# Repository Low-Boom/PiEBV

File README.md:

# PiEBV

A pulse-timing box for particle image velocimetry (PIV), built around a Raspberry Pi Pico 2 W. It
triggers two laser drivers and synchronizes up to six event cameras. It is controlled over USB,
and also over Wi-Fi after the network link is set up.

> **Hardware status:** Firmware timing has not yet been verified on a physical board. Complete the
> [first-board checks](docs/FIRST_BOARD_CHECKS.md#first-board-checks) before connecting a laser driver or camera.
> The network (Wi-Fi) link has not run on a board either: do the
> [network checks](docs/FIRST_BOARD_CHECKS.md#network-checks) before you rely on it.

## Quick start

With the assembled board, a Pico 2 W, a USB-C PD charger that supplies 15 V, and a micro-USB data
cable:

```
python -m pip install platformio
pio run
```

1. Follow the [first-board checks](docs/FIRST_BOARD_CHECKS.md#first-board-checks) before applying power or
   connecting equipment.
2. Flash `.pio/build/pico2w/firmware.uf2`: hold **BOOTSEL** while connecting the Pico's micro-USB
   cable, then copy the UF2 to the `RP2350` drive. Flash with the Pico out of the board or J17
   unplugged.
3. Seat the Pico components-up, USB toward the board's left edge. Set J10 to **2-3** and J18, J19
   and J21 to **1-2** for the 50 Ω scope checks; leave J11 empty until instructed to check the outputs.
4. Connect the 15 V charger to J17 and the Pico's micro-USB to the computer. Open the Pico's serial
   port, enable local echo, and send `*IDN?`. The reply starts with `PiEBV,`.
5. Follow [Hardware setup](docs/SETUP.md#hardware-setup) to check the laser outputs with a scope before
   connecting laser drivers or cameras.

**Contents:** [Quick start](#quick-start) · [Documentation](#documentation) ·
[What it does](#what-it-does) · [Safety](#safety) · [The board](#the-board) ·
[Connecting](#connecting) · [Most-used commands](#most-used-commands) ·
[Repository layout](#repository-layout)

---

## Documentation

The README gives the overview. The pages below give the detail.

| Page | What it holds | Who needs it |
|---|---|---|
| [docs/SAFETY.md](docs/SAFETY.md) | The safety rules in detail: starting and stopping, laser outputs, cameras and jumpers | Everyone, before the lasers are armed for the first time |
| [docs/SETUP.md](docs/SETUP.md) | Hardware setup step by step, first-board checks, jumpers, J12, seating the Pico, power | Anyone who sets up a board |
| [docs/CONNECTING.md](docs/CONNECTING.md) | USB serial, web GUI, Python scripting, network (Wi-Fi) | Operators and script writers |
| [docs/COMMANDS.md](docs/COMMANDS.md) | Command reference (SCPI): rules, commands, timing, status registers, errors, Wi-Fi set-up | Operators and script writers |
| [docs/TROUBLESHOOTING.md](docs/TROUBLESHOOTING.md) | Symptoms, likely causes and fixes | Anyone with a problem |
| [docs/FIRMWARE_BUILD.md](docs/FIRMWARE_BUILD.md) | Building from source, timing checks, protocol check, network check, signal simulation | Firmware developers |
| [Hardware.md](Hardware.md) | Hardware reference: pins, power, signal chains, connectors | Hardware developers |
| [docs/DESIGN_NOTES.md](docs/DESIGN_NOTES.md) | Design notes: index of the design pages in `docs/design/` (layout, power, signals, firmware, network link), Rev 2 changes | Hardware and firmware developers |
| [docs/design/NETWORK.md](docs/design/NETWORK.md) | Design of the network link: decisions, rules for `DISARM`, radio fault handling, verification | Firmware developers |
| [docs/FIRST_BOARD_CHECKS.md](docs/FIRST_BOARD_CHECKS.md) | The full first-board checks, with exact test points | Anyone who tests a newly assembled board |
| [docs/MANUFACTURING.md](docs/MANUFACTURING.md) | Fabrication and assembly notes | Anyone who orders or assembles a board |
| [docs/EVK4_HARNESS.md](docs/EVK4_HARNESS.md) | The EVK4 camera harness | Users of Prophesee EVK4 cameras |
| [fab/jlc/JLC_ORDER.md](fab/jlc/JLC_ORDER.md) | The JLCPCB order checklist | Anyone who orders a board |
| [tools/rev2/README.md](tools/rev2/README.md) | The scripts that build the Rev 2 board | Hardware developers |
| [tools/signal_sim/README.md](tools/signal_sim/README.md) | The transmission-line simulation of the timing nets | Hardware developers |

---

## What it does

| Output | Connector | What it is for |
|---|---|---|
| **Laser 1** (CH1) | BNC J7 | Trigger for the first laser driver: a 5 V pulse (with J18 set to match the input), of the set pulse width (`:PULS:WIDT`), at the set frequency (`:FREQ`) |
| **Laser 2** (CH2) | BNC J8 | Trigger for the second laser driver: the same pulse, starting exactly the set delay (`:PULS:DOUB:DEL`) after Laser 1 |
| **Sync** | Camera ports J1–J6 | A steady 1 MHz clock that all six cameras keep time by |
| **Trigger** (the marker) | Camera ports J1–J6 | A pulse at the same instant as every Laser 1 pulse. Each camera records it as a timestamp in its data. (Jumper J10 can switch the cameras to the Laser 1 pulse itself instead.) |
| **Pixel reset** | Camera ports J1–J6 | Holds the camera sensors blank between flash pairs. Controlled only by PiEBV (`:PIX:GATE`) |
| **External Sync Out** | BNC J12 | A copy of the camera trigger (the marker, or Laser 1 with J10 on 1-2) for other equipment: a 5 V pulse, with J21 set to match the input |

- Every signal to the cameras is **1.8 V** (IDS cameras, J22 open) or **3.3 V** (Prophesee EVK4
  cameras, J22 fitted). The laser outputs and External Sync Out are **5 V**.
- The camera signal level comes from a power mux (U20). Its default input is 1.8 V: with J22 open,
  two pull-up resistors in parallel (R34 and R70) select 1.8 V. A shunt on J22 pulls the select pin low and selects
  3.3 V.
- Each camera line has a **47 Ω series resistor on the board** (R52–R69), between the buffer and
  the camera port. It terminates the camera cable at the source. The camera cables need no
  resistors.
- The camera lines of each group have **equal length** on the board, from the buffer to the series
  resistor: Sync 74.082 mm, Trigger 43.584 mm, pixel reset 51.472 mm (spread below 0.001 mm in
  each group, KiCad's length reading).
- Times are set in steps of **6.667 ns** (one tick of the Pico's 150 MHz clock), or **3.333 ns**
  with a shunt on the clock jumper J20 (a 300 MHz overclock; see [Jumpers](#jumpers)).
  Every query returns the exact value the hardware will produce, so you never have to correct for
  the step size.
- Both laser pulses share one pulse width and one frequency.
- The firmware sets **no laser-driver limits** (pulse width, duty, spacing). Set what your driver is
  rated for. It only stops the pulses from running into each other.

PiEBV was designed for two **PicoLas LDP-V** laser-diode drivers (models 10-70 and 240-100) and six
**IDS uEye UE-39B0XCP-E** event cameras. Board revision 2 can also drive six **Prophesee EVK4**
cameras at 3.3 V (see the [EVK4 harness](docs/EVK4_HARNESS.md)). Other drivers with a 5 V trigger input should work too, with
the output mode (J18/J19) set to match their input.

---

## Safety

### The short version

1. **The lasers start off.** At every power-up and every reset the laser outputs are DISARMED. They
   pulse only after you send `:OUTP ON`.
2. **Typing `DISARM` stops them at once.** `:OUTP OFF` also stops them.
3. **Three things must all be true** for the lasers to pulse. Remove any one and they stop:
   - the firmware is ARMED;
   - a shunt is on **J11 pins 1-2** (or a closed E-stop switch is wired there);
   - a 15 V USB-C charger is plugged into **J17**.
4. **Unplugging the computer does not stop the lasers.** Use J11 or J17 for that. A lost network
   link does not stop them either. With Wi-Fi set up, `:OUTP ON` can also come from the network.
5. **Set each output's mode (J18, J19, J21) before you connect anything to it.**
6. **One laser driver per output.** Never split an output with a BNC tee, and never join J7 and J8.
7. **Cameras:** build the harness with wires 2, 3, 4, 5 and 7 only, and set every camera to sync
   slave.

The rules in detail are in [docs/SAFETY.md](docs/SAFETY.md).

---

## The board

The board is a **EuroCard, 160 × 100 mm**. Orientation used below: the board is landscape (160 mm
wide), seen from the top side. All connectors are on the two short edges: the Pico's micro-USB,
TP3 and, at the bottom, the USB-C connector J17 on the **left** edge, and only the three BNCs on
the **right** edge. The Pico plugs into two horizontal sockets at the top left, with its micro-USB at
the left edge, and the six camera ports run in one row along the bottom. The two USB ports are
labelled on the board: **`CONTROL / PROGRAM — PICO MICRO-USB`** (commands and firmware) and
**`POWER ONLY — USB-C PD 15 V`** (J17). The long (160 mm) edges have no parts within 2.5 mm, so the
board fits EuroCard card guides and slotted enclosures.

```
             +------------------------------------------------------------+
 Pico USB    |= Pico 2 W, in J15 (top row)                        J18 J7 =|  Laser 1 (BNC)
 = CONTROL   |  and J14 (bottom row)        J10 (trigger select)          |
             |= TP3 (1 MHz scope)  J20 (clock)                    J19 J8 =|  Laser 2 (BNC)
             |  J12 offset field            J11 (laser enable)            |
             |                                                   J21 J12 =|  External Sync Out (BNC)
 USB-C       |= J17                                                       |
 = POWER ONLY|       J1   J2   J3   J4   J5   J6   (camera ports)         |
             +------------------------------------------------------------+
```

(Not to scale. J18, J19 and J21 are the output-mode jumpers. J22, at the top centre, sets the camera signal level.
J23, the fan header, is at the bottom left, between mounting hole MH3 and camera port J1.
The status LEDs are near the top edge. Images of the board are in
[Hardware.md](Hardware.md#board-views).)

### Connectors

| Ref | What | Connect to | Notes |
|---|---|---|---|
| **J1–J6** | Camera ports 1–6 (2×5 IDC headers) | Each camera's 8-pin I/O cable (header pin *n* = camera pin *n*) | Pin 2, 7 ground · 3 pixel reset · 4 trigger · 5 sync · 1, 6, 8, 9, 10 not connected. All signals **1.8 V** (J22 open, IDS cameras) or **3.3 V** (J22 fitted, Prophesee EVK4 with the [EVK4 harness](docs/EVK4_HARNESS.md)). Each signal has a 47 Ω series resistor on the board. Pin 1 is the top-left pin. |
| **J7** | BNC, Laser 1 (CH1) | First laser driver's trigger input | Mode set by J18 |
| **J8** | BNC, Laser 2 (CH2) | Second laser driver's trigger input | Mode set by J19 |
| **J12** | BNC, External Sync Out | Equipment that must follow the camera trigger (50 Ω or Hi-Z input) | Mode set by J21. See [J12](docs/SETUP.md#j12--external-sync-out) |
| **J17** | USB-C, **power only** | A USB-C PD charger that offers 15 V | No data. Commands and firmware go through the Pico's own micro-USB. |
| **J10** | Camera trigger source (jumper) | A shunt | See [Jumpers](#jumpers) |
| **J11** | Laser enable (jumper) | A shunt, or a normally-closed E-stop switch | See [Jumpers](#jumpers) |
| **J18**, **J19**, **J21** | Output mode (jumpers; J18 = Laser 1, J19 = Laser 2, J21 = External Sync Out) | A shunt | See [Jumpers](#jumpers) |
| **J20** | Clock jumper, 2-pin header right of the Pico, below the J14 row | Nothing (150 MHz), or a shunt (300 MHz overclock) | See [Jumpers](#jumpers). Leave it open unless that Pico passed the soak test. |
| **TP3** | 2-pin header on the left edge, below the Pico | A scope | Pin 1 = the 1 MHz sync straight from the Pico (3.3 V) · pin 2 = ground |
| **J22** | Camera signal level, 2-pin header at the top centre | Nothing (1.8 V, IDS cameras), or a shunt (3.3 V, Prophesee EVK4) | See [Jumpers](#jumpers). **Never fit it with an IDS camera connected.** |
| **J23** | Fan supply, 2-pin header at the bottom left, marked `J23  FAN 12V` and `0.2 A MAX` | One 2-wire 12 V DC cooling fan of 40 mm, 200 mA maximum | Pin 1 (`+`, the top pin) = 12 V · pin 2 (`-`) = ground. The fan runs when the charger on J17 gives 15 V. There is no firmware control. The header has no key: connect the fan with the correct polarity. Do not fit a shunt on J23: it shorts the fan supply to ground. Do not connect a fan to the 12 V supply of the laser drivers. |
| **TP4–TP9** | Bare test pads at the top centre, marked `12V`, `5V`, `3V3`, `1V8`, `VCAM`, `GND` | A multimeter | Supply rails |

### Jumpers

Pin 1 always has the square pad. Change J22 with the power off.

| Jumper | Function | Positions | Default |
|---|---|---|---|
| **J10** | Camera trigger source | 1-2: every Laser 1 pulse (only while ARMED) · 2-3: the marker · none: no camera triggers | **2-3** |
| **J11** | Laser enable | 1-2: lasers enabled (the firmware must also be ARMED) · 2-3 or none: lasers off | **1-2** to run. Leave it empty until you check the outputs. |
| **J18** | Laser 1 output mode | 1-2: 50 Ω mode · 2-3: Hi-Z mode · none: wrong, always fit a shunt | **1-2** (for the LDP-V) |
| **J19** | Laser 2 output mode | as J18 | as J18 |
| **J21** | External Sync Out mode | 1-2: 50 Ω mode · 2-3: Hi-Z mode · none: wrong, always fit a shunt | **1-2** |
| **J20** | Clock jumper (2 pins) | open: 150 MHz, the rated clock · shunt: 300 MHz overclock | **open** |
| **J22** | Camera signal level (2 pins) | open: 1.8 V (IDS cameras) · shunt: 3.3 V (Prophesee EVK4) | **open** |

The board labels, the E-stop wiring and the full description of each jumper are in
[docs/SETUP.md](docs/SETUP.md#jumpers).

### Status LEDs

The LEDs near the top edge show the state of the board.

| LED | Colour | Meaning when lit |
|---|---|---|
| `12V OK` | green | The USB-C charger gave 15 V and the 12 V supply of the output drivers is good. Dark: the laser outputs and J12 cannot pulse. |
| `ARMED` | red | The lasers can fire: the firmware is ARMED, J11 is on 1-2 (or the E-stop switch is closed) and `12V OK` is lit. |
| `3V3` | blue | The camera ports are at 3.3 V (J22 fitted). Dark: 1.8 V. |
| `L1`, `L2` | red | A pulse left the Laser 1 / Laser 2 output driver. One flash for each pulse; on continuously above about 70 pulses a second. |
| `SYNC` | yellow | A pulse left the External Sync Out driver (J12). |

The LEDs are indicators only. Do not use a dark `ARMED` LED as proof that the lasers are off: an
LED can fail. To make the lasers safe, send `DISARM`, open J11 or unplug J17.

### Pico and power

Seat the Pico components up, with its micro-USB connector at the left edge. Connect a USB-C PD
charger that offers 15 V to J17. Connect the Pico's micro-USB to the computer. A 12 V cooling fan
on J23 runs when the charger gives 15 V. On a 5 V-only charger it normally does not turn. The details are in
[Seating the Pico](docs/SETUP.md#seating-the-pico) and [Power](docs/SETUP.md#power).

---

## Connecting

1. Use the Pico's micro-USB port. J17 carries power only.
2. Open the Pico's serial port. The port needs no driver.
   ```
   pio device monitor --echo                 # PlatformIO; add -p COM7 if needed
   ```
3. Turn on local echo. The firmware does not echo what you type.
4. Do not use 1200 baud. 115200 is usual.
5. Type `*IDN?` and press Enter. The reply starts with `PiEBV,`.
6. Type `:SYST:ECHO ON` to get a reply to each setting and each error in the terminal. Without
   it, a setting gives no reply.

Other terminals, the web GUI and Python scripting are in [docs/CONNECTING.md](docs/CONNECTING.md).

### Network (Wi-Fi)

A Pico 2 W can also take the commands over Wi-Fi, on TCP port 4242 of an existing network (open,
or WPA2 with a shared passphrase). Set it up one time over USB, with the lasers DISARMED:

```
:SYST:COMM:WLAN:SSID "Lab Network"
:SYST:COMM:WLAN:PASS "correct horse"
:SYST:COMM:WLAN ON
:SYST:ERR?                       ->  0,"No error"
:SYST:COMM:WLAN:LINK?;IPAD?      ->  CONNECTED,"";"192.168.1.37"
```

Then connect to the address that `:SYST:COMM:WLAN:IPAD?` gives, for example
`python tools/piebv_gui/piebv_gui.py --connect socket://192.168.1.37:4242`. The web GUI has a card
for the same set-up.

- The network link has **no password and no encryption**: each computer that can reach the board
  can arm the lasers. Use it only on a network that you control.
- A lost network link does not disarm.
- The link has not been tested on a board.

The details and the limits are in [docs/CONNECTING.md](docs/CONNECTING.md#network-wi-fi).

## Most-used commands

| Command | Unit | Default | What it sets or returns |
|---|---|---|---|
| `:FREQ <f>`, `:FREQ?` | Hz | 1000 | How many pulse pairs per second |
| `:PULS:WIDT <t>`, `:PULS:WIDT?` | s | 100 ns | Length of both laser pulses |
| `:PULS:DOUB:DEL <t>`, `:PULS:DOUB:DEL?` | s | 10 µs | Time from the start of the Laser 1 pulse to the start of the Laser 2 pulse. `0` makes them start together. |
| `:OUTP ON` | – | disarmed | Allow the laser pulses (arm) |
| `DISARM` | – | – | Stop the laser pulses at once; recognised anywhere in what you type. `:OUTP OFF` also disarms. |
| `:OUTP?` | – | – | The arm state: `0` or `1` |
| `:SYST:ERR?` | – | – | The next entry of the error queue, or `0,"No error"` |
| `:SYST:ECHO ON` | – | off | A reply to each setting and error, for a terminal |
| `*IDN?` | – | – | Board and firmware version (the git commit it was built from) |
| `*RST` | – | – | Disarm and set the default settings |
| `:SYST:COMM:WLAN …` | – | off | The Wi-Fi state and set-up ([details](docs/COMMANDS.md#wi-fi-set-up)) |
| `:SYST:HELP:HEAD?` | – | – | The list of all commands |

- Times are in seconds and frequencies in hertz. Add a suffix: `:PULS:WIDT 100 NS`,
  `:PULS:DOUB:DEL 10 US`, `:FREQ 2 KHZ`. A number without a suffix is in seconds or hertz.
- A query ends in `?` and returns the realized value, for example `1.000000000E-07` for 100 ns.
- A setting gives no reply. An error goes into the error queue: read it with `:SYST:ERR?`.
- One line can hold more than one command, separated by `;`:
  `:FREQ 15;:PULS:WIDT 100 NS;DOUB:DEL 10 US`.

All commands, limits and errors are in [docs/COMMANDS.md](docs/COMMANDS.md). If something
does not work, see [docs/TROUBLESHOOTING.md](docs/TROUBLESHOOTING.md).

---

## Repository layout

| Path | Contents |
|---|---|
| `src/` | Firmware: `main.cpp` (start-up, arming, crash watchdog), `protocol.*` (SCPI commands, on USB and on the network link), `net_link.*` (Wi-Fi link of a Pico 2 W), `tcp_link.*` (its TCP server), `wifi_config.h` (Wi-Fi set-up values and flash record), `pulse_timing.h` (timing maths and checks), `pio_pulse.*` (PIO programs), `sync_clock.*` (1 MHz SYNC clock), `clock_mode.*` (clock jumper: 150 or 300 MHz at boot), `laser_gate.*` (laser output gate), `board.h` (pin map) |
| `platformio.ini` | Build configuration (`pico2w` and `pico2` builds) |
| `tools/piebv_example.py` | Python example script |
| `tools/piebv_gui/` | Web GUI: settings, timing chart and console in the browser |
| `tools/piebv_sim/` | Simulator: the firmware's command code built for a computer, for trying the GUI and scripts without a board, and `scpi_check.py`, which checks the SCPI replies |
| `tools/timing_check/` | Timing checks run on a computer |
| `tools/net_check/` | Checks of the network link's connection handling, run on a computer: against a model of lwIP, and against lwIP's own sources |
| `tools/signal_sim/` | Transmission-line simulation of the timing nets (KiCad's ngspice) |
| `PiEBV_Pico.kicad_pro` / `.kicad_sch` / `.kicad_pcb` | **Current hardware:** KiCad project of the 4-layer board |
| `Hardware.md` | [Full hardware reference](Hardware.md) |
| `fab/` | Manufacturing: master parts list `fab/PiEBV_Pico_BOM.csv` (with the design-constraint notes), gerbers and drill files, and `fab/jlc/` JLCPCB assembly files and [order checklist](fab/jlc/JLC_ORDER.md) |
| `libs/`, `fp-lib-table`, `sym-lib-table` | Project-local KiCad symbols and footprints |
| `tools/jlc_cpl/` | Corrects the JLC placement file to JLC's own footprints (see its README) |
| `tools/eurocard/` | Builds the Rev 1 EuroCard board from the 126 × 126 mm hand layout: placement, KiCadRoutingTools routing, checks (see its README) |
| `tools/rev2/` | Builds the current Rev 2 board from the Rev 1 EuroCard board: camera level select, series resistors in the camera lines, new camera routing with equal lengths, status LEDs, power islands, cooling fan supply, checks, fab export (see its README) |
| `docs/` | The documentation pages (see [Documentation](#documentation)), the [EVK4 camera harness](docs/EVK4_HARNESS.md) and the board images (`docs/img/`) |
| `docs/reports/` | Earlier design review reports |

## License

PiEBV is distributed under **OCL v1.1 + RnD v1**: the
[Open Community License v1.1](https://github.com/OpenCommunityLicence/OpenCommunityLicence)
with the add-on condition
[Research & Development v1](https://github.com/OpenCommunityLicence/OpenCommunityLicence/blob/main/addons/RnD-v1.md).
The full text is in [LICENSE](LICENSE). The board silkscreen shows `OCL v1.1 + RnD v1`.

Summary (for orientation only; the text in [LICENSE](LICENSE) applies):

- **Non-commercial use:** you may use, copy, modify and hack PiEBV. If you distribute a
  derivative, you must distribute it under OCL and keep the RnD v1 condition.
- **Commercial use:** only for internal research and development: experiments and prototyping
  to develop your own creations that are not derived from PiEBV. You must not use PiEBV or its
  derivatives for manufacturing outside this scope without a separate business licence. You
  must not copy or replicate them for a commercial purpose without a separate business licence
  or repair licence, except for your internal right to repair.
- **Text and data mining:** systematic or automated text or data mining of PiEBV is not
  permitted without explicit permission.
- Components that are under a licence that is not compatible with OCL keep their own licence.

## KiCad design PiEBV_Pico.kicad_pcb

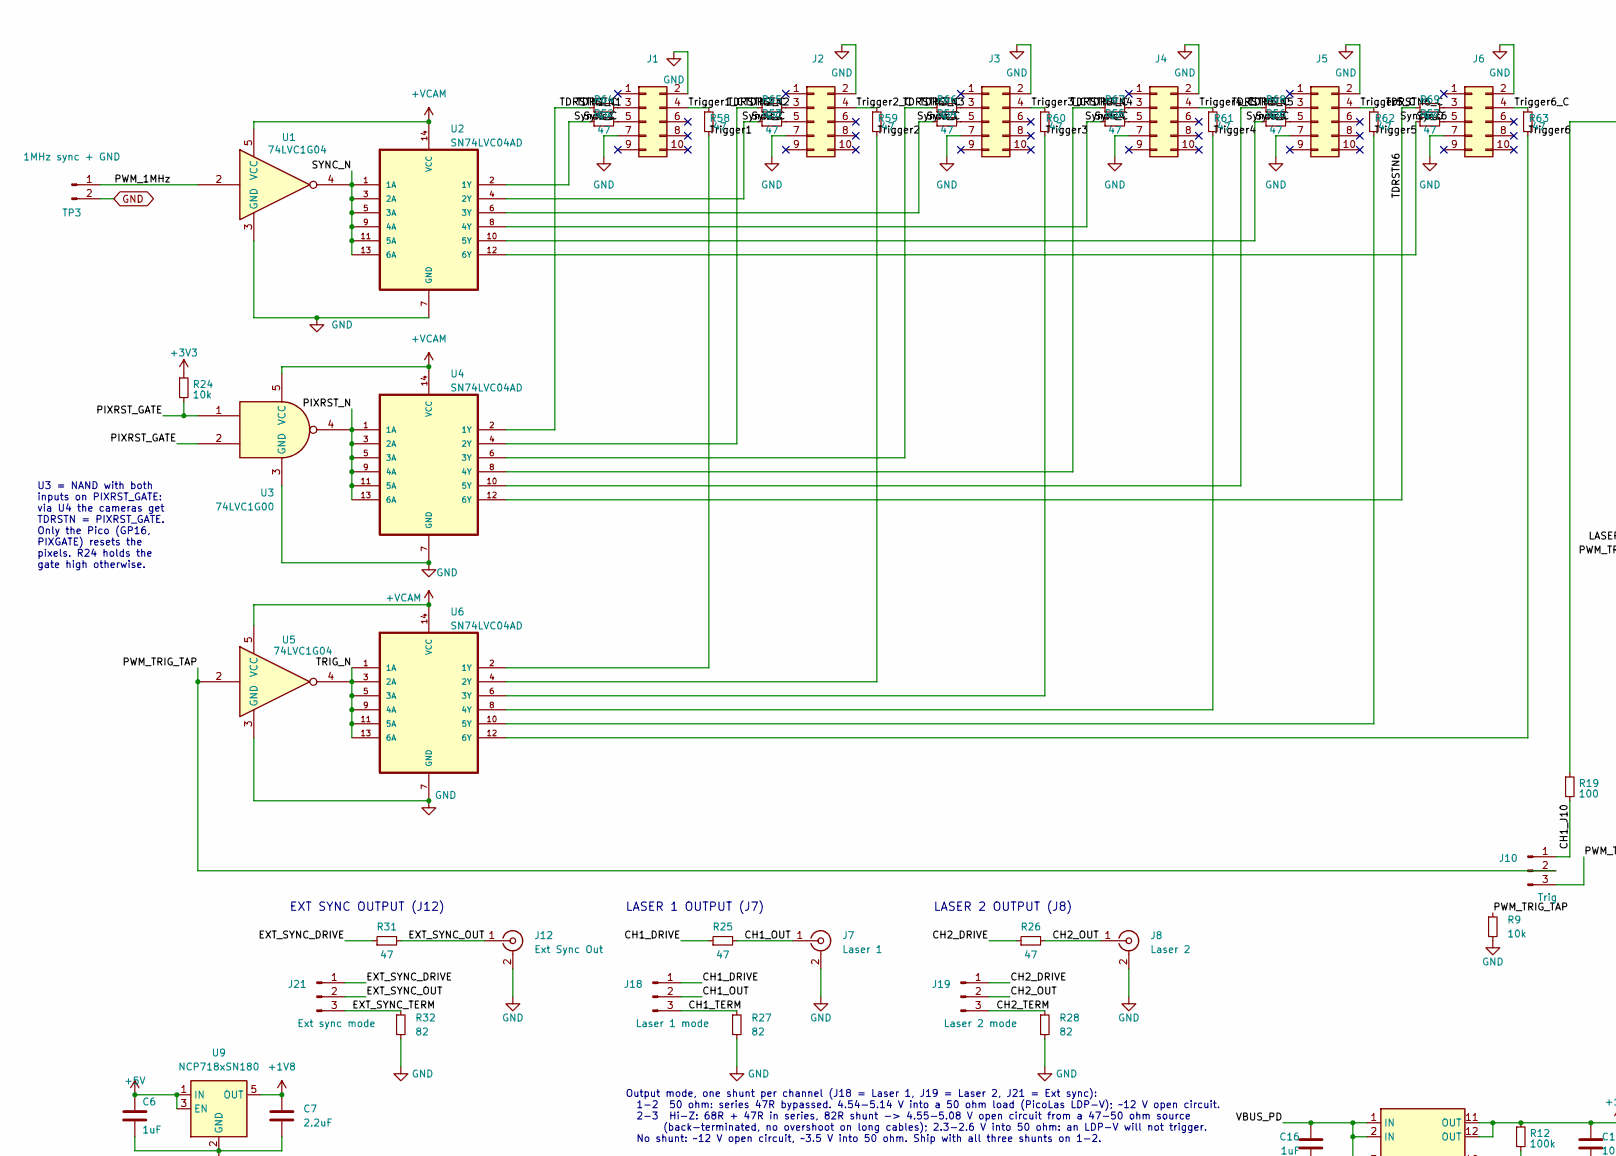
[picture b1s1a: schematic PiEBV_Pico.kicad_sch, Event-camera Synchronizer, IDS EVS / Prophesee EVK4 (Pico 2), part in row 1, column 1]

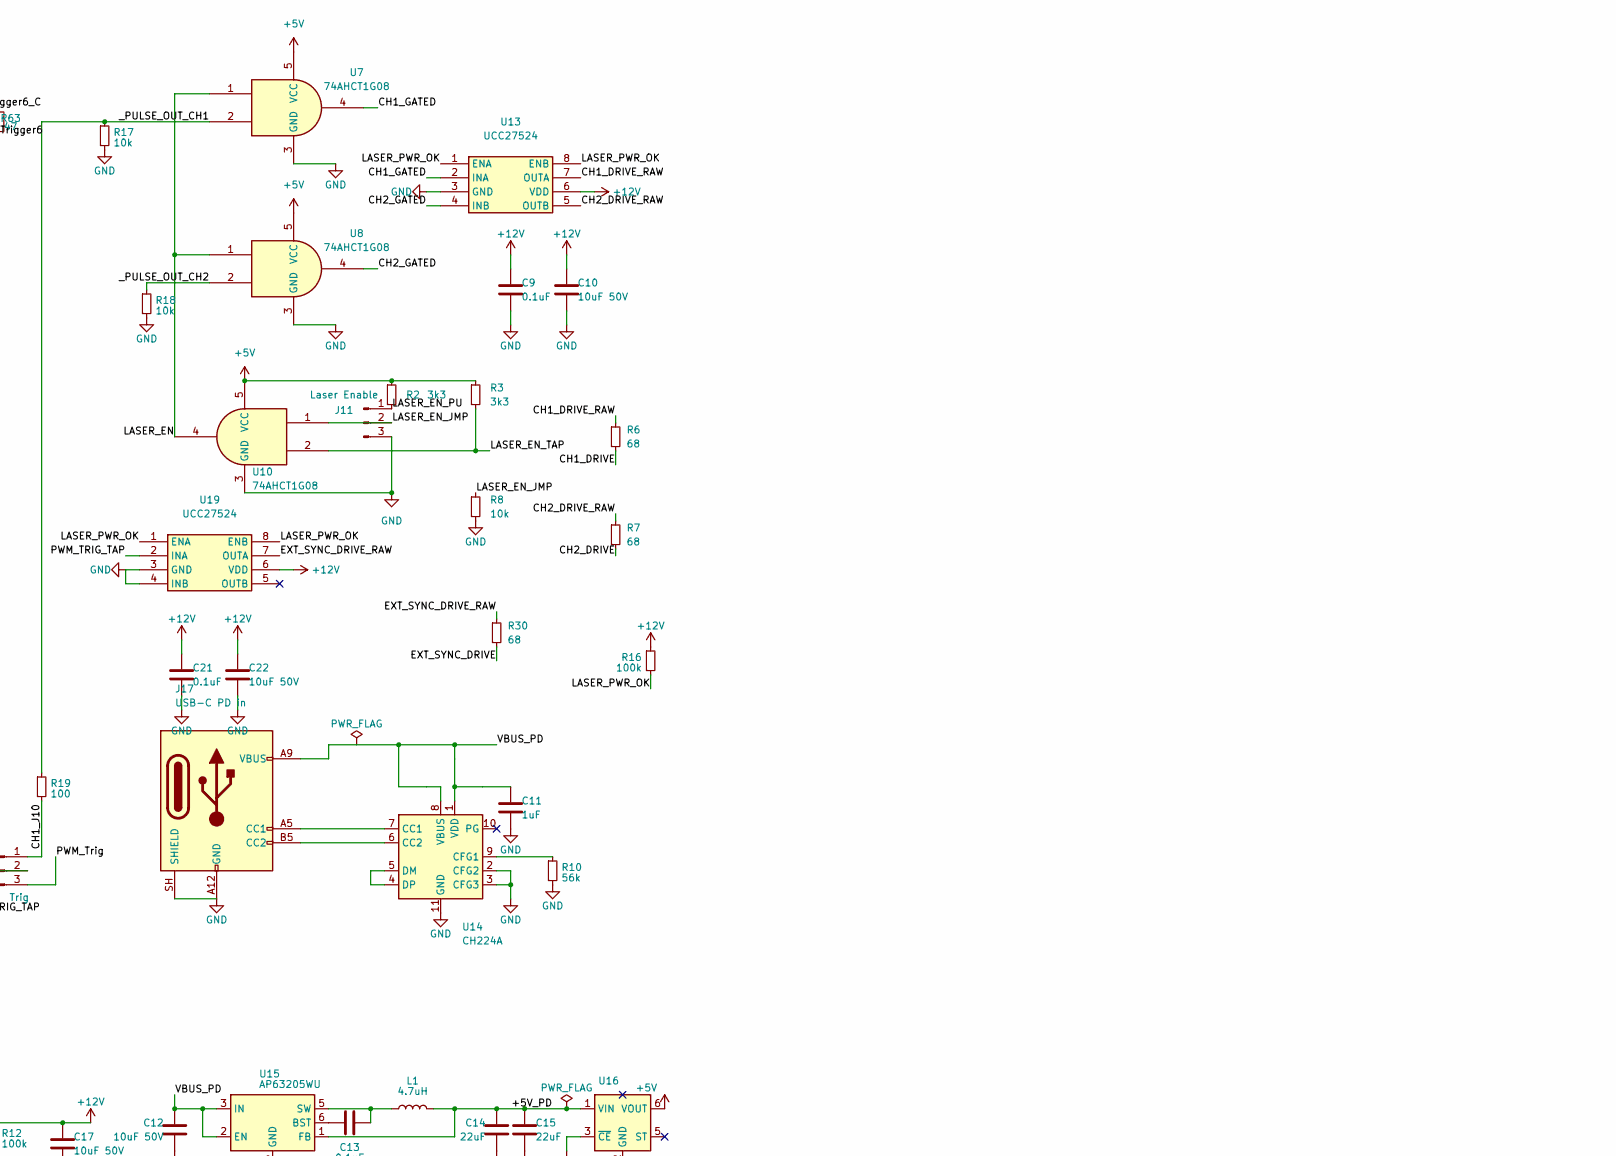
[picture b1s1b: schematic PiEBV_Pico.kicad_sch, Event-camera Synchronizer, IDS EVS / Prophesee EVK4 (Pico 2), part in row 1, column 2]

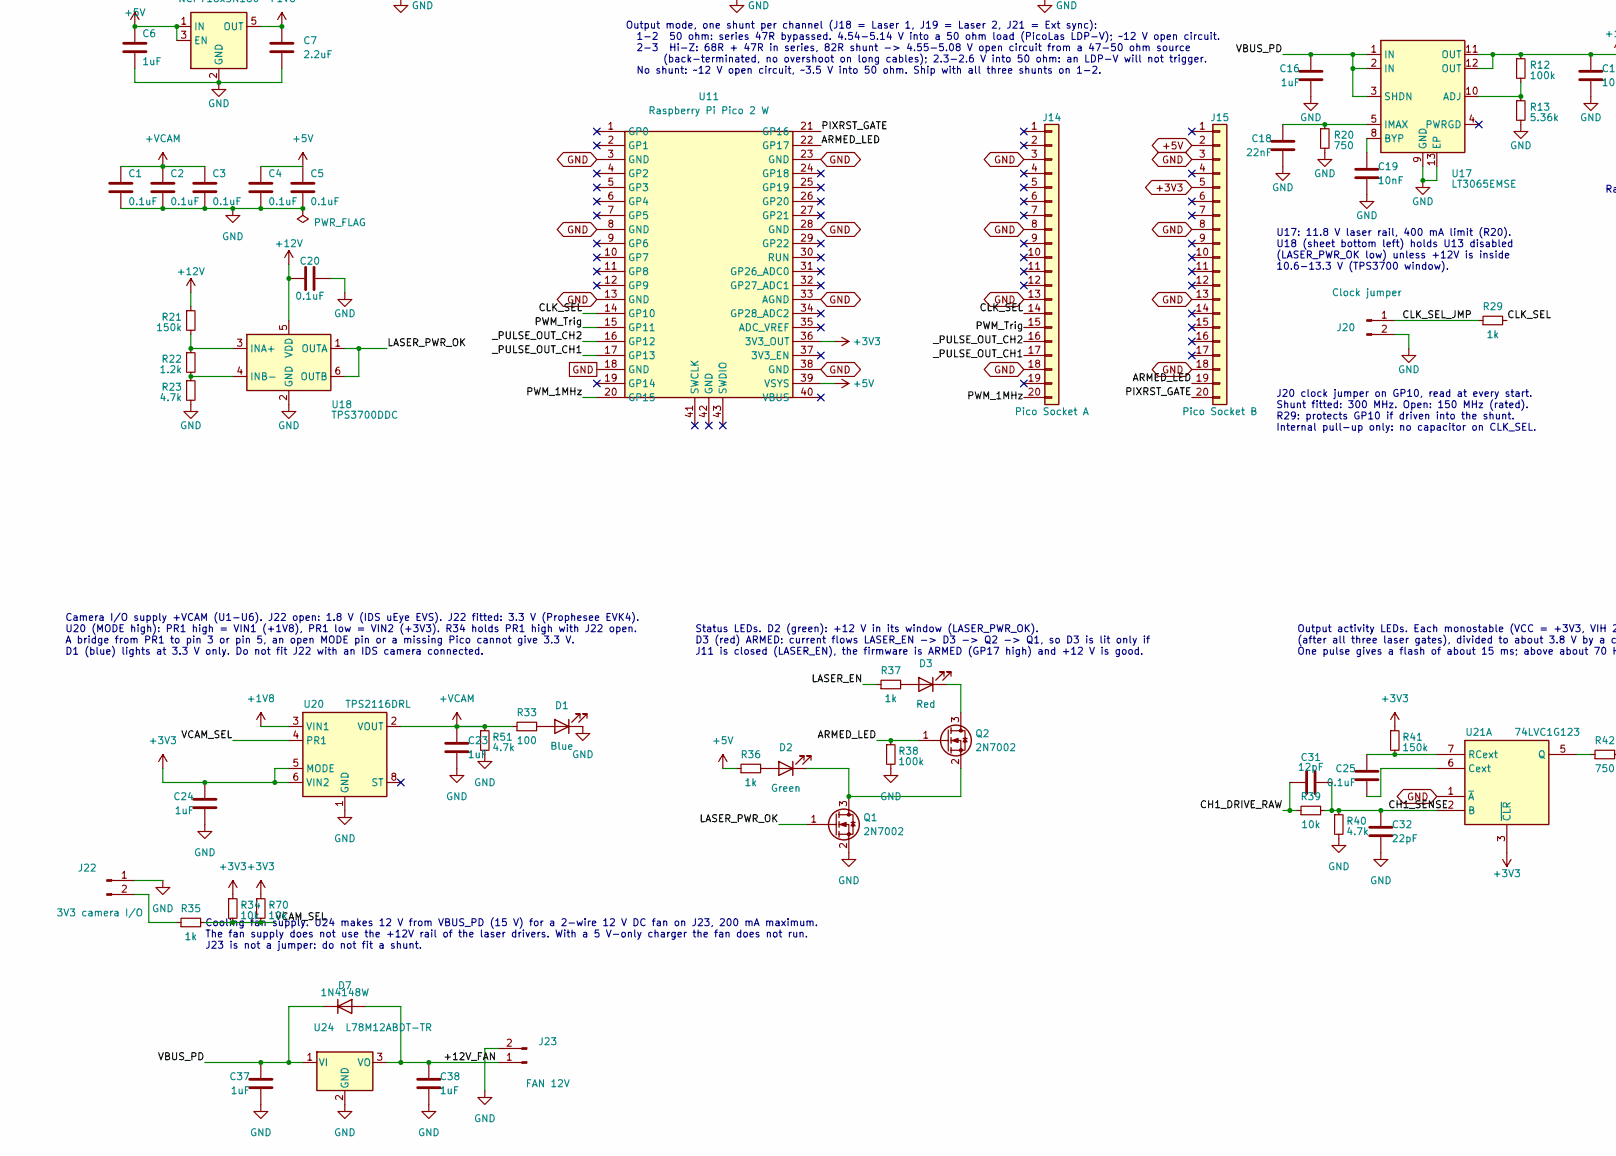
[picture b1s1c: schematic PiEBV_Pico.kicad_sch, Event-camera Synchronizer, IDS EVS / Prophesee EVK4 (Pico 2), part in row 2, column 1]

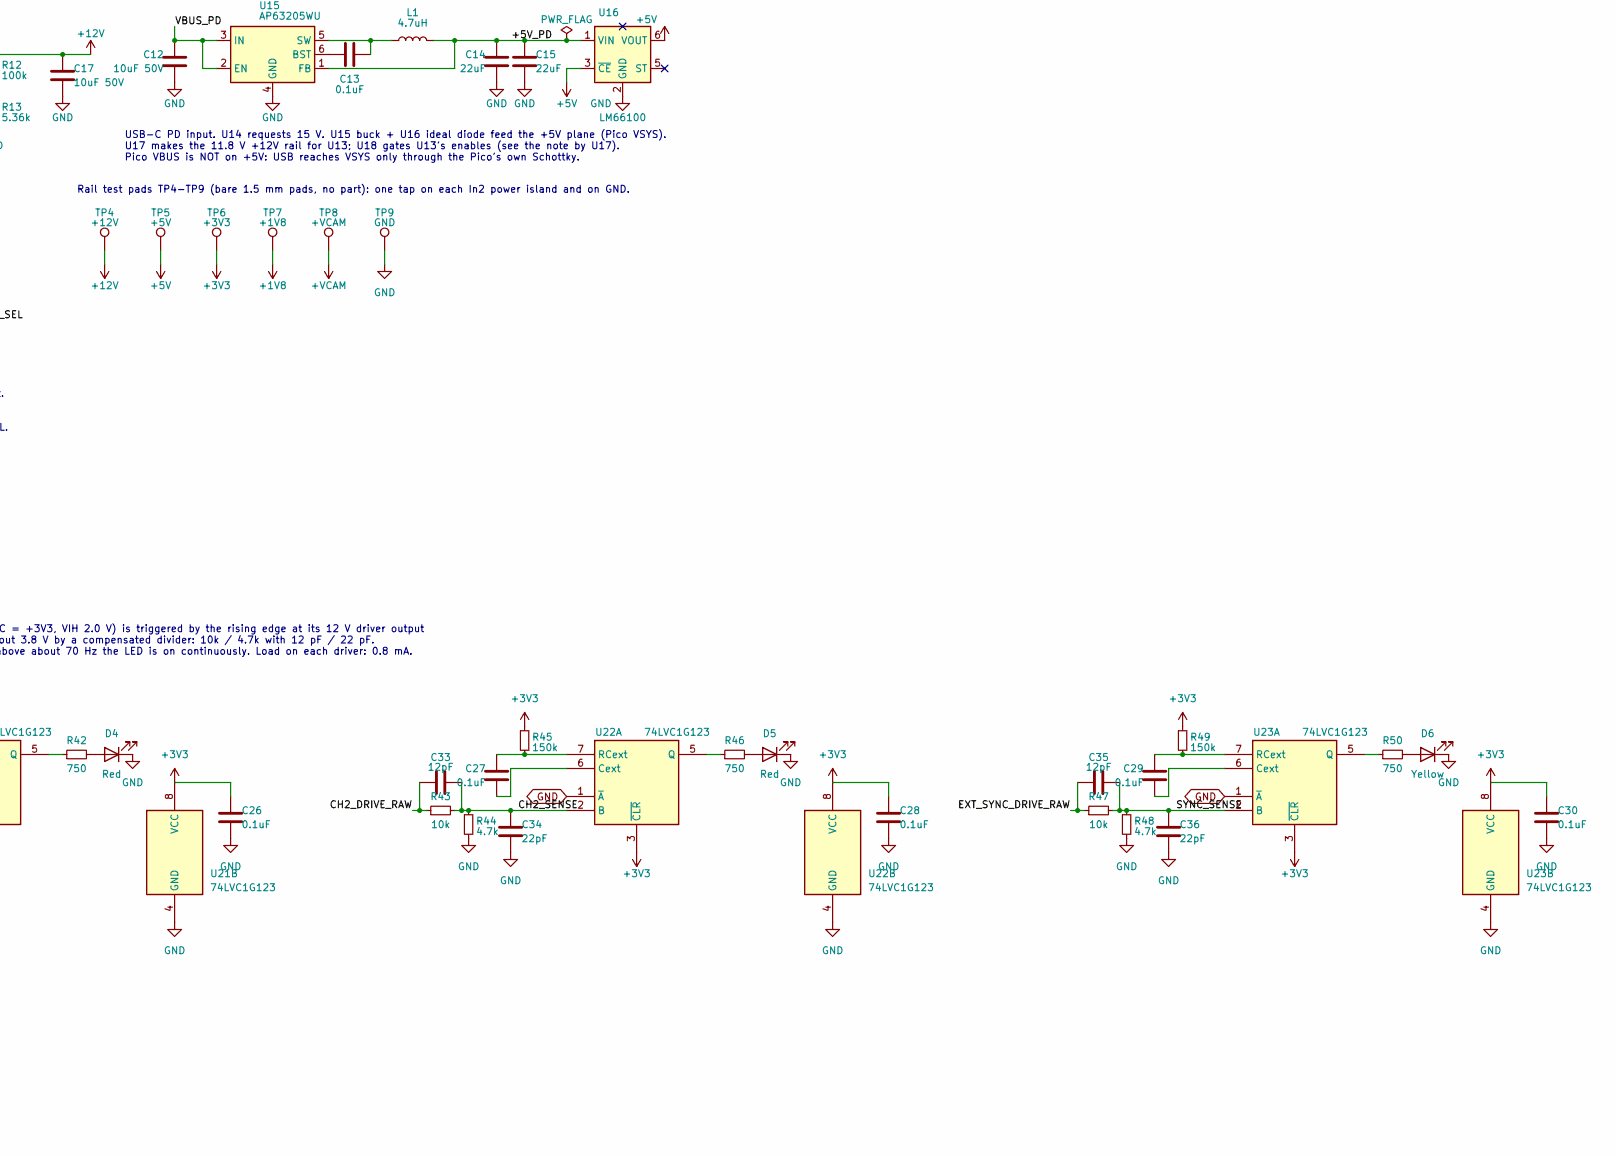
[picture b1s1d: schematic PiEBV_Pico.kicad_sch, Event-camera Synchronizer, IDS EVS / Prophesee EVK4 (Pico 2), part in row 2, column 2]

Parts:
C1, C2, C3, C4, C5, C9, C13, C20, C21, C25, C26, C27, C28, C29, C30: 0.1uF; C_0805_2012Metric_Pad1.18x1.45mm_HandSolder
C6, C11, C16, C23, C24, C37, C38: 1uF; C_0805_2012Metric_Pad1.18x1.45mm_HandSolder
C7: 2.2uF; C_0805_2012Metric_Pad1.18x1.45mm_HandSolder
C10, C12, C17, C22: 10uF 50V; C_1206_3216Metric_Pad1.33x1.80mm_HandSolder
C14, C15: 22uF; C_0805_2012Metric_Pad1.18x1.45mm_HandSolder
C18: 22nF; C_0805_2012Metric_Pad1.18x1.45mm_HandSolder
C19: 10nF; C_0805_2012Metric_Pad1.18x1.45mm_HandSolder
C31, C33, C35: 12pF; C_0805_2012Metric_Pad1.18x1.45mm_HandSolder
C32, C34, C36: 22pF; C_0805_2012Metric_Pad1.18x1.45mm_HandSolder
D1: Blue; LED_0805_2012Metric_Pad1.15x1.40mm_HandSolder
D2: Green; LED_0805_2012Metric_Pad1.15x1.40mm_HandSolder
D3, D4, D5: Red; LED_0805_2012Metric_Pad1.15x1.40mm_HandSolder
D6: Yellow; LED_0805_2012Metric_Pad1.15x1.40mm_HandSolder
D7: 1N4148W; D_SOD-123
J1, J2, J3, J4, J5, J6: Conn_02x05_Odd_Even; IDC-Header_2x05_P2.54mm_Vertical
J7: Laser 1; BNC_Kinghelm_KH-BNC50-3511_Horizontal
J8: Laser 2; BNC_Kinghelm_KH-BNC50-3511_Horizontal
J10: Trig; PinHeader_1x03_P2.54mm_Vertical
J11: Laser Enable; PinHeader_1x03_P2.54mm_Vertical
J12: Ext Sync Out; BNC_Kinghelm_KH-BNC50-3511_Horizontal
J14: Pico Socket A; PinSocket_1x20_P2.54mm_Vertical
J15: Pico Socket B; PinSocket_1x20_P2.54mm_Vertical
J17: USB-C PD in; USB_C_Receptacle_HRO_TYPE-C-31-M-17_EdgeTrim
J18: Laser 1 mode; PinHeader_1x03_P2.54mm_Vertical
J19: Laser 2 mode; PinHeader_1x03_P2.54mm_Vertical
J20: Clock jumper; PinHeader_1x02_P2.54mm_Vertical
J21: Ext sync mode; PinHeader_1x03_P2.54mm_Vertical
J22: 3V3 camera I/O; PinHeader_1x02_P2.54mm_Vertical
J23: FAN 12V; PinHeader_1x02_P2.54mm_Vertical
L1: 4.7uH; L_Cenker_CKCS4030
Q1, Q2: 2N7002; SOT-23
R2, R3: 3k3; R_0805_2012Metric_Pad1.20x1.40mm_HandSolder
R6, R7, R30: 68; R_2512_6332Metric_Pad1.40x3.35mm_HandSolder
R8, R9, R17, R18, R24, R34, R39, R43, R47, R70: 10k; R_0805_2012Metric_Pad1.20x1.40mm_HandSolder
R10: 56k; R_0805_2012Metric_Pad1.20x1.40mm_HandSolder
R12, R16, R38: 100k; R_0805_2012Metric_Pad1.20x1.40mm_HandSolder
R13: 5.36k; R_0805_2012Metric_Pad1.20x1.40mm_HandSolder
R19, R33: 100; R_0805_2012Metric_Pad1.20x1.40mm_HandSolder
R20, R42, R46, R50: 750; R_0805_2012Metric_Pad1.20x1.40mm_HandSolder
R21, R41, R45, R49: 150k; R_0805_2012Metric_Pad1.20x1.40mm_HandSolder
R22: 1.2k; R_0805_2012Metric_Pad1.20x1.40mm_HandSolder
R23, R40, R44, R48, R51: 4.7k; R_0805_2012Metric_Pad1.20x1.40mm_HandSolder
R25, R26, R31: 47; R_2512_6332Metric_Pad1.40x3.35mm_HandSolder
R27, R28, R32: 82; R_2512_6332Metric_Pad1.40x3.35mm_HandSolder
R29, R35, R36, R37: 1k; R_0805_2012Metric_Pad1.20x1.40mm_HandSolder
R52, R53, R54, R55, R56, R57, R58, R59, R60, R61, R62, R63, R64, R65, R66, R67, R68, R69: 47; R_0805_2012Metric_Pad1.20x1.40mm_HandSolder
TP3: 1MHz sync + GND; PinHeader_1x02_P2.54mm_Horizontal_EdgeTrim
TP4: +12V; TestPoint_Pad_D1.5mm
TP5: +5V; TestPoint_Pad_D1.5mm
TP6: +3V3; TestPoint_Pad_D1.5mm
TP7: +1V8; TestPoint_Pad_D1.5mm
TP8: +VCAM; TestPoint_Pad_D1.5mm
TP9: GND; TestPoint_Pad_D1.5mm
U1, U5: 74LVC1G04; SOT-23-5_HandSoldering
U2, U4, U6: SN74LVC04AD; SOIC127P600X175-14N
U3: 74LVC1G00; SOT-23-5_HandSoldering
U7, U8, U10: 74AHCT1G08; SOT-23-5_HandSoldering
U9: NCP718xSN180; SOT-23-5_HandSoldering
U11: Raspberry Pi Pico 2 W
U13, U19: UCC27524; SOIC-8_3.9x4.9mm_P1.27mm
U14: CH224A; SSOP-10-1EP_3.9x4.9mm_P1mm_EP2.1x3.3mm
U15: AP63205WU; TSOT-23-6_HandSoldering
U16: LM66100; SOT-363_SC-70-6
U17: LT3065EMSE; MSOP-12-1EP_3x4.039mm_P0.65mm_EP1.651x2.845mm
U18: TPS3700DDC; SOT-23-6
U20: TPS2116DRL; SOT-583-8
U21, U22, U23: 74LVC1G123; SSOP-8_2.95x2.8mm_P0.65mm
U24: L78M12ABDT-TR; TO-252-2

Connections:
+1V8: C7.1, TP7.1, U9.5 (VCC), U20.3 (VIN1)
+3V3: C24.1, C26.1, C28.1, C30.1, J15.5, R24.1, R34.1, R41.1, R45.1, R49.1, R70.1, TP6.1, U11.36 (3V3_OUT), U20.5 (MODE), U20.6 (VIN2), U21.3 (~CLR), U21.8 (VCC), U22.3 (~CLR), U22.8 (VCC), U23.3 (~CLR), U23.8 (VCC)
+5V: C4.1, C5.1, C6.1, J15.2, R2.1, R3.1, R36.1, TP5.1, U7.5 (VCC), U8.5 (VCC), U9.1 (IN), U9.3 (GND), U10.5 (VCC), U11.39 (VSYS), U16.3 (~CE), U16.6 (VOUT)
+5V_PD: C14.1, C15.1, L1.2, U15.1 (FB), U16.1 (VIN)
+12V: C9.2, C10.2, C17.1, C20.1, C21.2, C22.2, R12.1, R16.1, R21.1, TP4.1, U13.6 (VDD), U17.11 (OUT), U17.12 (OUT), U18.5 (VDD), U19.6 (VDD)
+12V_FAN: C38.1, D7.2 (A), J23.1, U24.3 (VO)
+VCAM: C1.1, C2.1, C3.1, C23.1, R33.1, R51.1, TP8.1, U1.5 (VCC), U2.14 (VCC), U3.5 (VCC), U4.14 (VCC), U5.5 (VCC), U6.14 (VCC), U20.2 (VOUT), U20.7 (VOUT)
ARMED_LED: J15.19, Q2.1 (G), R38.1, U11.22 (GP17)
CH1_DRIVE: J18.1, R6.2, R25.1
CH1_DRIVE_RAW: C31.1, R6.1, R39.1, U13.7 (OUTA)
CH1_GATED: U7.4, U13.2 (INA)
CH1_J10: J10.1, R19.2
CH1_OUT: J7.1 (In), J18.2, R25.2
CH1_SENSE: C31.2, C32.1, R39.2, R40.1, U21.2 (B)
CH1_TERM: J18.3, R27.1
CH2_DRIVE: J19.1, R7.2, R26.1
CH2_DRIVE_RAW: C33.1, R7.1, R43.1, U13.5 (OUTB)
CH2_GATED: U8.4, U13.4 (INB)
CH2_OUT: J8.1 (In), J19.2, R26.2
CH2_SENSE: C33.2, C34.1, R43.2, R44.1, U22.2 (B)
CH2_TERM: J19.3, R28.1
CLK_SEL: J14.14, R29.2, U11.14 (GP10)
CLK_SEL_JMP: J20.1, R29.1
EXT_SYNC_DRIVE: J21.1, R30.2, R31.1
EXT_SYNC_DRIVE_RAW: C35.1, R30.1, R47.1, U19.7 (OUTA)
EXT_SYNC_OUT: J12.1 (In), J21.2, R31.2
EXT_SYNC_TERM: J21.3, R32.1
GND: C1.2, C2.2, C3.2, C4.2, C5.2, C6.2, C7.2, C9.1, C10.1, C11.2, C12.2, C14.2, C15.2, C16.2, C17.2, C18.2, C19.2, C20.2, C21.1, C22.1, C23.2, C24.2, C26.2, C28.2, C30.2, C32.2, C34.2, C36.2, C37.2, C38.2, D1.1 (K), D4.1 (K), D5.1 (K), D6.1 (K), J1.2, J1.7, J2.2, J2.7, J3.2, J3.7, J4.2, J4.7, J5.2, J5.7, J6.2, J6.7, J7.2 (Ext), J8.2 (Ext), J11.3, J12.2 (Ext), J14.3, J14.8, J14.13, J14.18, J15.3, J15.8, J15.13, J15.18, J17.A12 (GND), J17.B12 (GND), J17.SH (SHIELD), J20.2, J22.1, J23.2, Q1.2 (S), R8.2, R9.2, R10.2, R13.2, R17.2, R18.2, R20.2, R23.2, R27.2, R28.2, R32.2, R38.2, R40.2, R44.2, R48.2, R51.2, TP3.2, TP9.1, U1.3 (GND), U2.7 (GND), U3.3 (GND), U4.7 (GND), U5.3 (GND), U6.7 (GND), U7.3 (GND), U8.3 (GND), U9.2 (GND), U10.3 (GND), U11.3 (GND), U11.8 (GND), U11.13 (GND), U11.18 (GND), U11.23 (GND), U11.28 (GND), U11.33 (AGND), U11.38 (GND), U13.3 (GND), U14.2 (CFG2), U14.3 (CFG3), U14.11 (GND), U15.4 (GND), U16.2 (GND), U17.9 (GND), U17.13 (EP), U18.2 (GND), U19.3 (GND), U19.4 (INB), U20.1 (GND), U21.1 (~A), U21.4 (GND), U22.1 (~A), U22.4 (GND), U23.1 (~A), U23.4 (GND), U24.2 (GND)
LASER_EN: R37.1, U7.1, U8.1, U10.4
LASER_EN_JMP: J11.2, R8.1, U10.1
LASER_EN_PU: J11.1, R2.2
LASER_EN_TAP: R3.2, U10.2
LASER_PWR_OK: Q1.1 (G), R16.2, U13.1 (ENA), U13.8 (ENB), U18.1 (OUTA), U18.6 (OUTB), U19.1 (ENA), U19.8 (ENB)
unnamed: D1.2 (A), R33.2
unnamed: D2.2 (A), R36.2
unnamed: D2.1 (K), Q1.3 (D), Q2.2 (S)
unnamed: D3.2 (A), R37.2
unnamed: D3.1 (K), Q2.3 (D)
unnamed: D4.2 (A), R42.2
unnamed: D5.2 (A), R46.2
unnamed: D6.2 (A), R50.2
unnamed: J17.A5 (CC1), U14.7 (CC1)
unnamed: J17.B5 (CC2), U14.6 (CC2)
unnamed: J22.2, R35.1
unnamed: R10.1, U14.9 (CFG1)
unnamed: U14.4 (DP), U14.5 (DM)
unnamed: C13.1, U15.6 (BST)
unnamed: C13.2, L1.1, U15.5 (SW)
unnamed: R12.2, R13.1, U17.10 (ADJ)
unnamed: C19.1, U17.8 (BYP)
unnamed: C18.1, R20.1, U17.5 (IMAX)
unnamed: R21.2, R22.1, U18.3 (INA+)
unnamed: R22.2, R23.1, U18.4 (INB-)
unnamed: C25.2, U21.6 (Cext)
unnamed: R42.1, U21.5 (Q)
unnamed: C25.1, R41.2, U21.7 (RCext)
unnamed: C27.2, U22.6 (Cext)
unnamed: R46.1, U22.5 (Q)
unnamed: C27.1, R45.2, U22.7 (RCext)
unnamed: C29.2, U23.6 (Cext)
unnamed: R50.1, U23.5 (Q)
unnamed: C29.1, R49.2, U23.7 (RCext)
PIXRST_GATE: J15.20, R24.2, U3.1 (NC), U3.2, U11.21 (GP16)
PIXRST_N: U3.4, U4.1 (1A), U4.3 (2A), U4.5 (3A), U4.9 (4A), U4.11 (5A), U4.13 (6A)
PWM_1MHz: J14.20, TP3.1, U1.2, U11.20 (GP15)
PWM_TRIG_TAP: J10.2, R9.1, U5.2, U19.2 (INA)
PWM_Trig: J10.3, J14.15, U11.15 (GP11)
SYNC_N: U1.4, U2.1 (1A), U2.3 (2A), U2.5 (3A), U2.9 (4A), U2.11 (5A), U2.13 (6A)
SYNC_SENSE: C35.2, C36.1, R47.2, R48.1, U23.2 (B)
Sync1: R52.1, U2.2 (1Y)
Sync1_C: J1.5, R52.2
Sync2: R53.1, U2.4 (2Y)
Sync2_C: J2.5, R53.2
Sync3: R54.1, U2.6 (3Y)
Sync3_C: J3.5, R54.2
Sync4: R55.1, U2.8 (4Y)
Sync4_C: J4.5, R55.2
Sync5: R56.1, U2.10 (5Y)
Sync5_C: J5.5, R56.2
Sync6: R57.1, U2.12 (6Y)
Sync6_C: J6.5, R57.2
TDRSTN1: R64.1, U4.2 (1Y)
TDRSTN1_C: J1.3, R64.2
TDRSTN2: R65.1, U4.4 (2Y)
TDRSTN2_C: J2.3, R65.2
TDRSTN3: R66.1, U4.6 (3Y)
TDRSTN3_C: J3.3, R66.2
TDRSTN4: R67.1, U4.8 (4Y)
TDRSTN4_C: J4.3, R67.2
TDRSTN5: R68.1, U4.10 (5Y)
TDRSTN5_C: J5.3, R68.2
TDRSTN6: R69.1, U4.12 (6Y)
TDRSTN6_C: J6.3, R69.2
TRIG_N: U5.4, U6.1 (1A), U6.3 (2A), U6.5 (3A), U6.9 (4A), U6.11 (5A), U6.13 (6A)
Trigger1: R58.2, U6.2 (1Y)
Trigger1_C: J1.4, R58.1
Trigger2: R59.2, U6.4 (2Y)
Trigger2_C: J2.4, R59.1
Trigger3: R60.2, U6.6 (3Y)
Trigger3_C: J3.4, R60.1
Trigger4: R61.2, U6.8 (4Y)
Trigger4_C: J4.4, R61.1
Trigger5: R62.2, U6.10 (5Y)
Trigger5_C: J5.4, R62.1
Trigger6: R63.2, U6.12 (6Y)
Trigger6_C: J6.4, R63.1
VBUS_PD: C11.1, C12.1, C16.1, C37.1, D7.1 (K), J17.A9 (VBUS), J17.B9 (VBUS), U14.1 (VDD), U14.8 (VBUS), U15.2 (EN), U15.3 (IN), U17.1 (IN), U17.2 (IN), U17.3 (SHDN), U24.1 (VI)
VCAM_SEL: R34.2, R35.2, R70.2, U20.4 (PR1)
_PULSE_OUT_CH1: J14.17, R17.1, R19.1, U7.2, U11.17 (GP13)
_PULSE_OUT_CH2: J14.16, R18.1, U8.2, U11.16 (GP12)

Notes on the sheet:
USB-C PD input. U14 requests 15 V. U15 buck + U16 ideal diode feed the +5V plane (Pico VSYS). U17 makes the 11.8 V +12V rail for U13; U18 gates U13's enables (see the note by U17). Pico VBUS is NOT on +5V: USB reaches VSYS only through the Pico's own Schottky.
LASER 1 OUTPUT (J7)
LASER 2 OUTPUT (J8)
Output mode, one shunt per channel (J18 = Laser 1, J19 = Laser 2, J21 = Ext sync): 1-2 50 ohm: series 47R bypassed. 4.54-5.14 V into a 50 ohm load (PicoLas LDP-V); ~12 V open circuit. 2-3 Hi-Z: 68R + 47R in series, 82R shunt -> 4.55-5.08 V open circuit from a 47-50 ohm source (back-terminated, no o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
U3 = NAND with both inputs on PIXRST_GATE: via U4 the cameras get TDRSTN = PIXRST_GATE. Only the Pico (GP16, PIXGATE) resets the pixels. R24 holds the gate high otherwise.
U17: 11.8 V laser rail, 400 mA limit (R20). U18 (sheet bottom left) holds U13 disabled (LASER_PWR_OK low) unless +12V is inside 10.6-13.3 V (TPS3700 window).
J20 clock jumper on GP10, read at every start. Shunt fitted: 300 MHz. Open: 150 MHz (rated). R29: protects GP10 if driven into the shunt. Internal pull-up only: no capacitor on CLK_SEL.
EXT SYNC OUTPUT (J12)
Cooling fan supply. U24 makes 12 V from VBUS_PD (15 V) for a 2-wire 12 V DC fan on J23, 200 mA maximum. The fan supply does not use the +12V rail of the laser drivers. With a 5 V-only charger the fan does not run. J23 is not a jumper: do not fit a shunt.
Camera I/O supply +VCAM (U1-U6). J22 open: 1.8 V (IDS uEye EVS). J22 fitted: 3.3 V (Prophesee EVK4). U20 (MODE high): PR1 high = VIN1 (+1V8), PR1 low = VIN2 (+3V3). R34 holds PR1 high with J22 open. A bridge from PR1 to pin 3 or pin 5, an open MODE pin or a missing Pico cannot give 3.3 V. D1 (blue)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
Status LEDs. D2 (green): +12 V in its window (LASER_PWR_OK). D3 (red) ARMED: current flows LASER_EN -> D3 -> Q2 -> Q1, so D3 is lit only if J11 is closed (LASER_EN), the firmware is ARMED (GP17 high) and +12 V is good.
Output activity LEDs. Each monostable (VCC = +3V3, VIH 2.0 V) is triggered by the rising edge at its 12 V driver output (after all three laser gates), divided to about 3.8 V by a compensated divider: 10k / 4.7k with 12 pF / 22 pF. One pulse gives a flash of about 15 ms; above about 70 Hz the LED is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
Rail test pads TP4-TP9 (bare 1.5 mm pads, no part): one tap on each In2 power island and on GND.

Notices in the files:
PiEBV_Pico.kicad_pcb:
PiEBV Rev 2  (C) 2026 Louis M. Edelman, Chris Willert
